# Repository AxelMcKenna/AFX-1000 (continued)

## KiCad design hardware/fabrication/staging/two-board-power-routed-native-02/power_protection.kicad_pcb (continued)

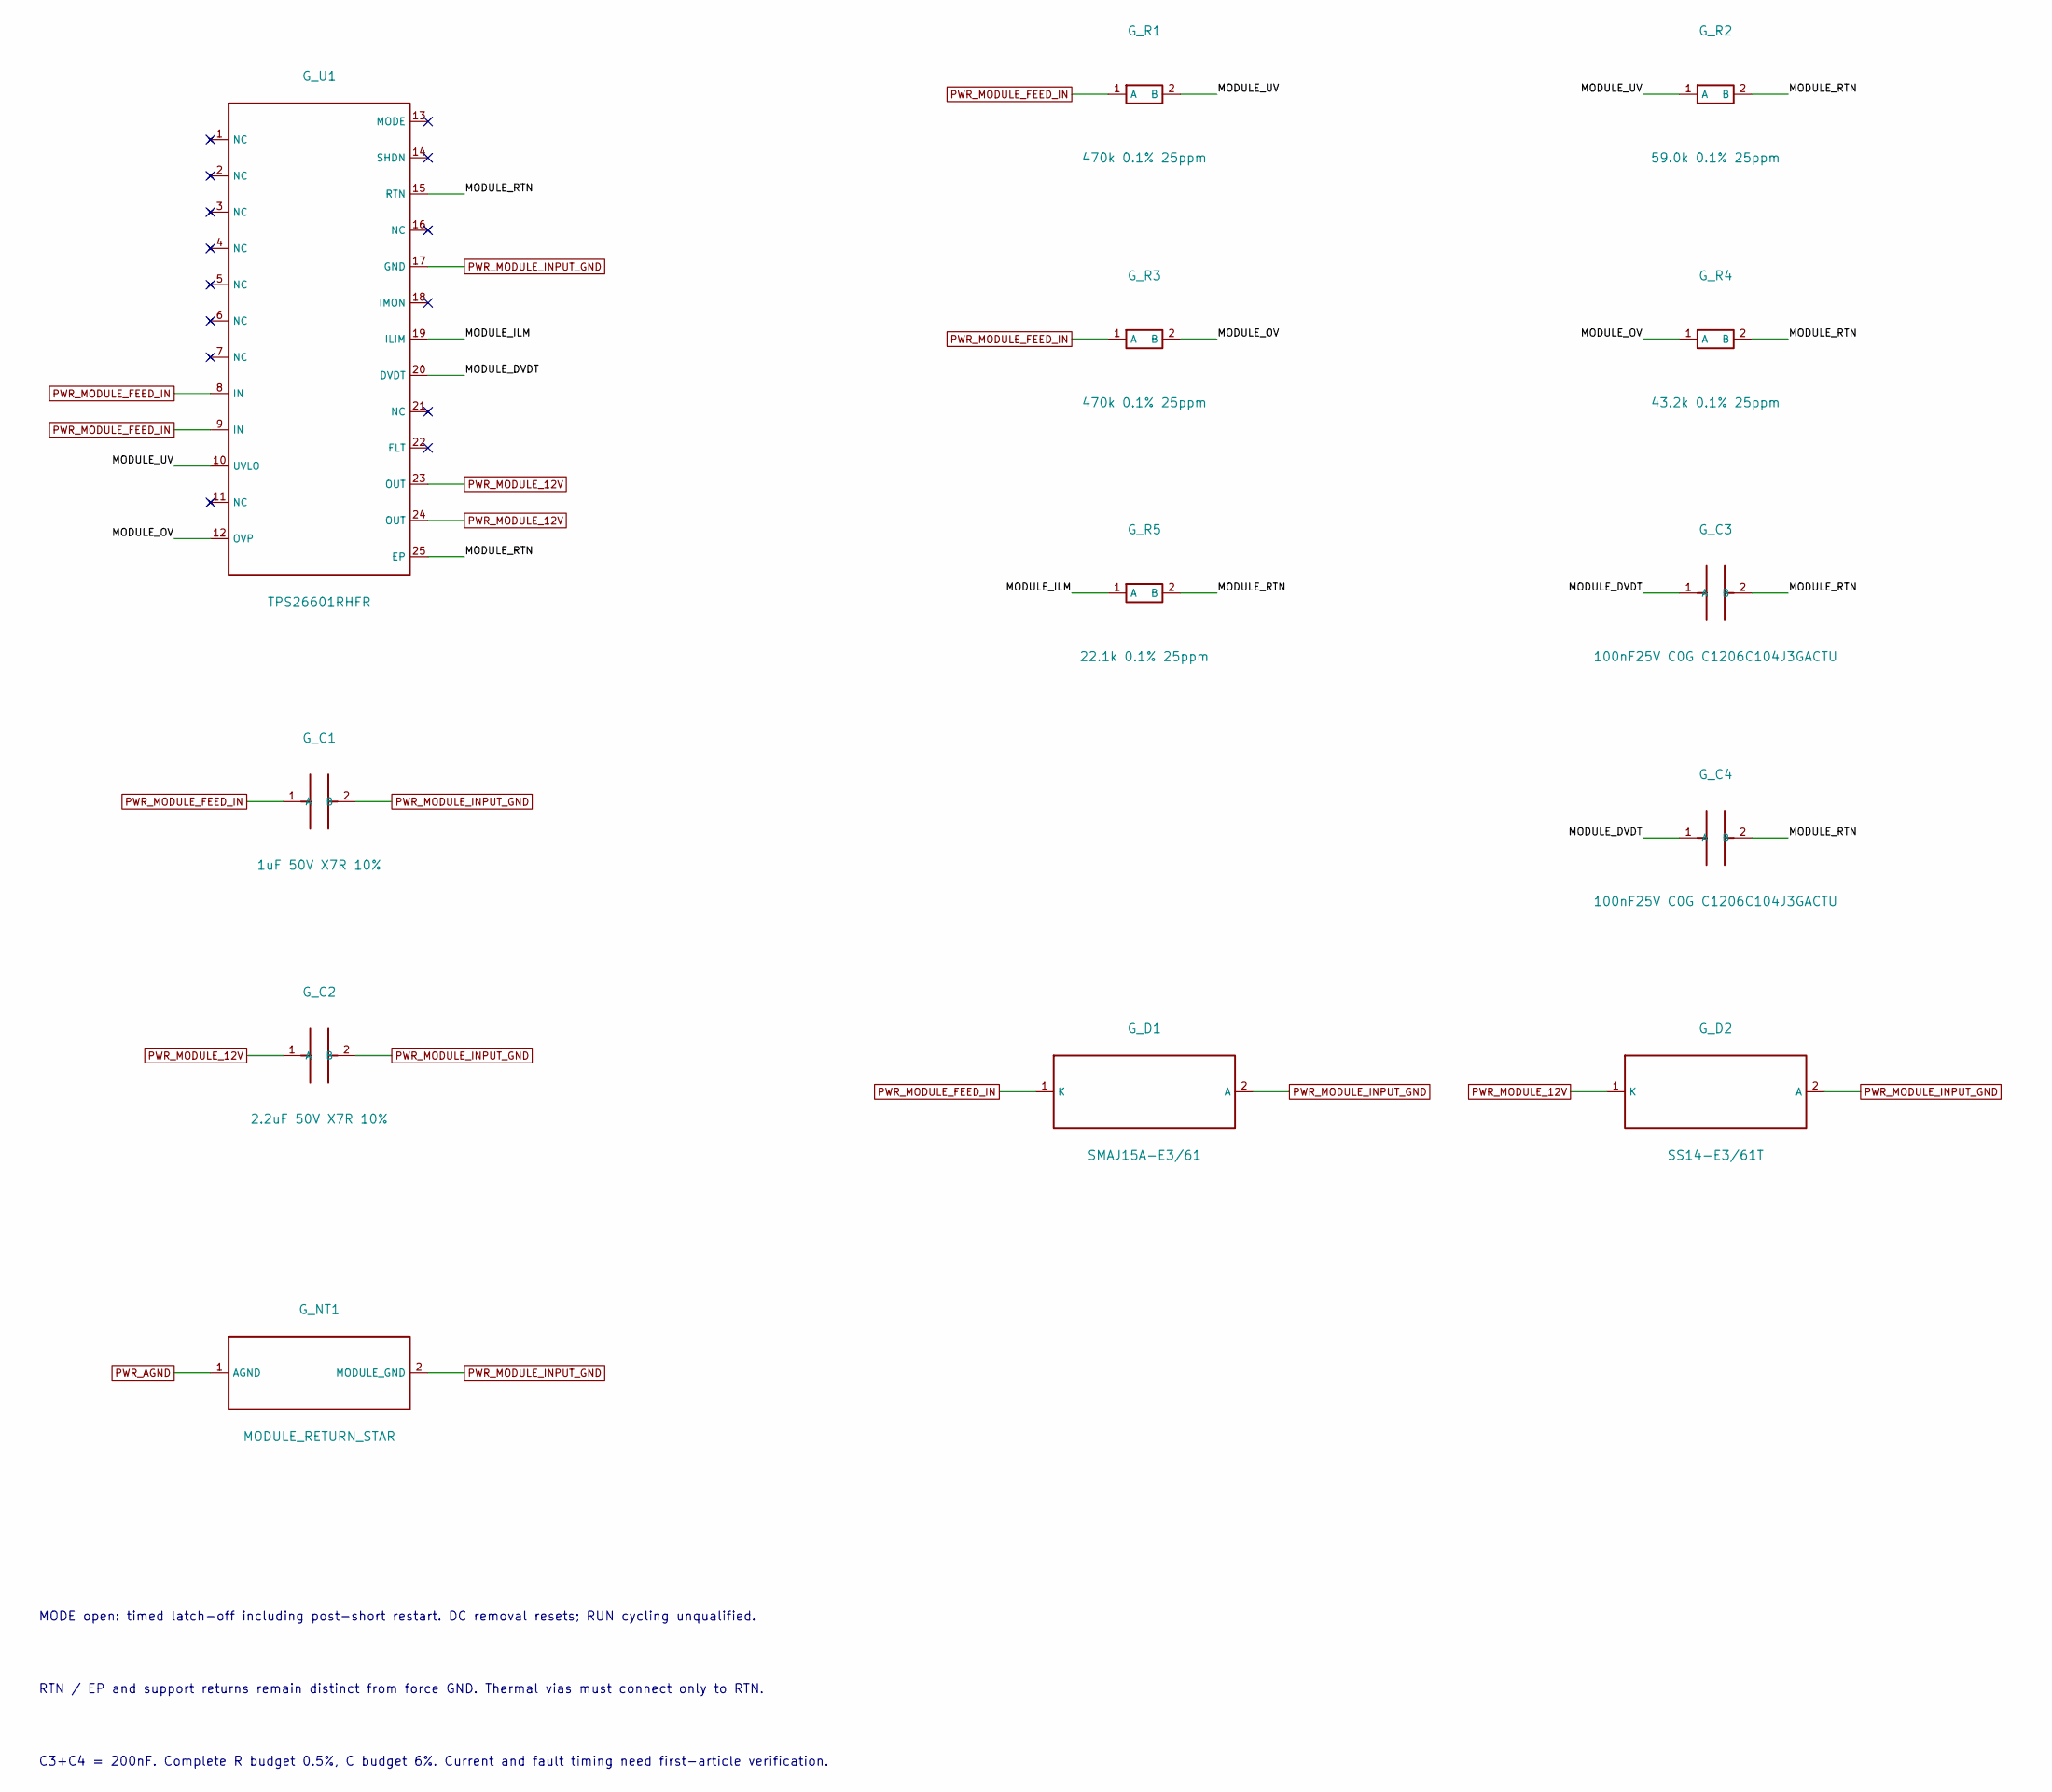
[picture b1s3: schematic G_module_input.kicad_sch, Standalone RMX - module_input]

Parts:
G_C1: 1uF 50V X7R 10%; C_0805_2012Metric
G_C2: 2.2uF 50V X7R 10%; C_1206_3216Metric
G_C3, G_C4: 100nF25V C0G C1206C104J3GACTU; PROPOSED_KEMET1206_LevelB
G_D1: SMAJ15A-E3/61; D_SMA
G_D2: SS14-E3/61T; D_SMA
G_NT1: MODULE_RETURN_STAR; Return_Star
G_R1, G_R3: 470k 0.1% 25ppm; R_0603_1608Metric
G_R2: 59.0k 0.1% 25ppm; R_0603_1608Metric
G_R4: 43.2k 0.1% 25ppm; R_0603_1608Metric
G_R5: 22.1k 0.1% 25ppm; R_0603_1608Metric
G_U1: TPS26601RHFR; TI_RHF0024A

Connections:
/G_module_input/MODULE_DVDT: G_C3.1 (A), G_C4.1 (A), G_U1.20 (DVDT)
/G_module_input/MODULE_ILM: G_R5.1 (A), G_U1.19 (ILIM)
/G_module_input/MODULE_OV: G_R3.2 (B), G_R4.1 (A), G_U1.12 (OVP)
/G_module_input/MODULE_RTN: G_C3.2 (B), G_C4.2 (B), G_R2.2 (B), G_R4.2 (B), G_R5.2 (B), G_U1.15 (RTN), G_U1.25 (EP)
/G_module_input/MODULE_UV: G_R1.2 (B), G_R2.1 (A), G_U1.10 (UVLO)
PWR_AGND: G_NT1.1 (AGND); also elsewhere on the board
PWR_MODULE_12V: G_C2.1 (A), G_D2.1 (K), G_U1.23 (OUT), G_U1.24 (OUT); also elsewhere on the board
PWR_MODULE_FEED_IN: G_C1.1 (A), G_D1.1 (K), G_R1.1 (A), G_R3.1 (A), G_U1.8 (IN), G_U1.9 (IN); also elsewhere on the board
PWR_MODULE_INPUT_GND: G_C1.2 (B), G_C2.2 (B), G_D1.2 (A), G_D2.2 (A), G_NT1.2 (MODULE_GND), G_U1.17 (GND); also elsewhere on the board

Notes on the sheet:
MODE open: timed latch-off including post-short restart. DC removal resets; RUN cycling unqualified.
RTN / EP and support returns remain distinct from force GND. Thermal vias must connect only to RTN.
C3+C4 = 200nF. Complete R budget 0.5%, C budget 6%. Current and fault timing need first-article verification.

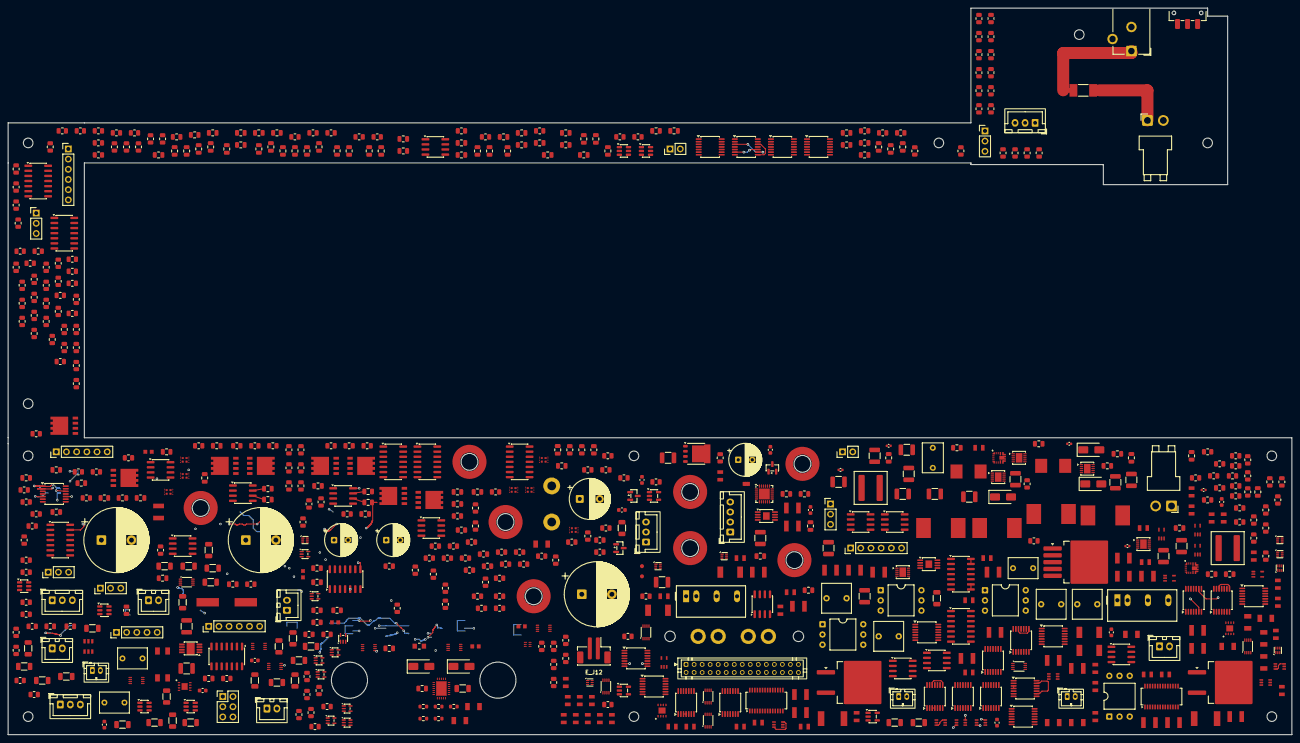
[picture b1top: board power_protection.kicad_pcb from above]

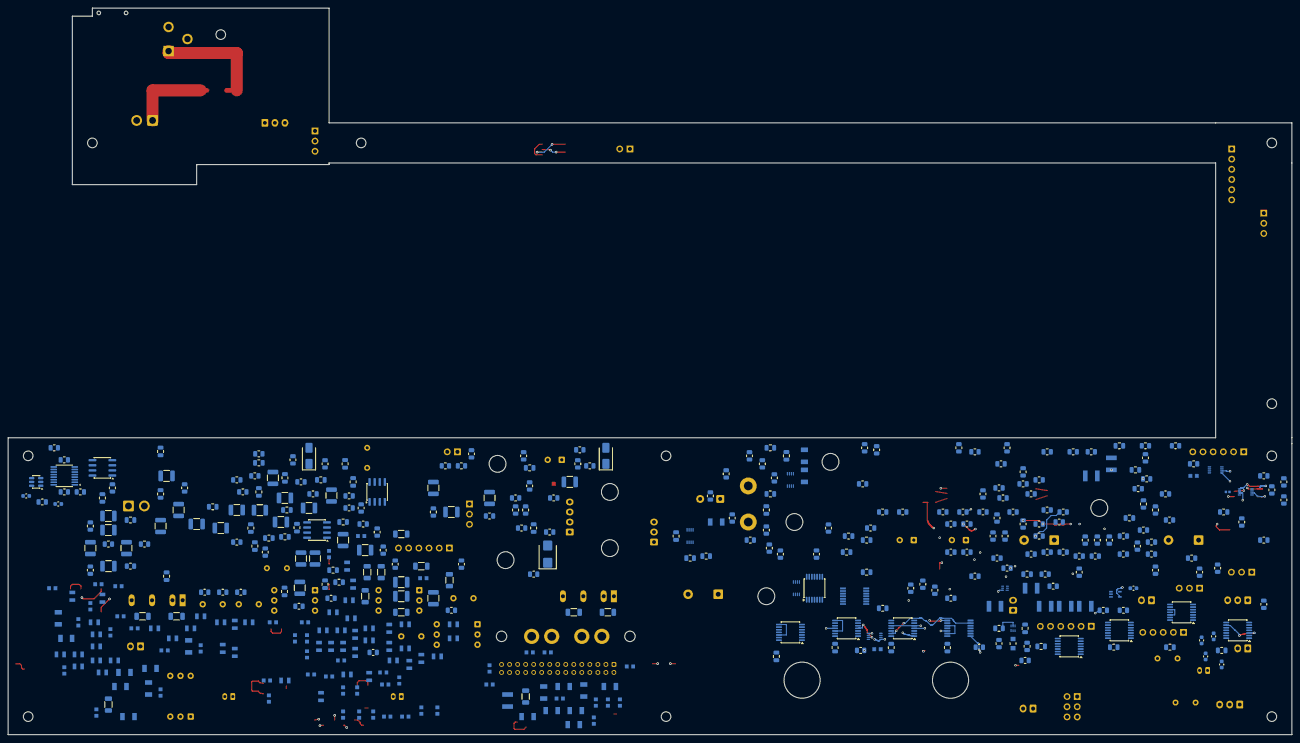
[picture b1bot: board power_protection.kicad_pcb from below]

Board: 8 copper layers, 320.0 x 181.1 mm, 1105 parts (410 on the bottom side), 635 nets.

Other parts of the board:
H_NEW1: PROPOSED_NPTH; H_NEW1
H_NEW2: PROPOSED_NPTH; H_NEW2
H_NEW3: PROPOSED_NPTH; H_NEW3
H_NEW4: PROPOSED_NPTH; H_NEW4
H_NEW5: PROPOSED_NPTH; H_NEW5
H_NEW6: PROPOSED_NPTH; H_NEW6
H_NEW7: PROPOSED_NPTH; H_NEW7
H_NEW8: PROPOSED_NPTH; H_NEW8
H_NEW9: PROPOSED_NPTH; H_NEW9
H_NEW10: PROPOSED_NPTH; H_NEW10
H_NEW11: PROPOSED_NPTH; H_NEW11
H_TOUCH1: PROPOSED_NPTH; H_TOUCH1
H_TOUCH2: PROPOSED_NPTH; H_TOUCH2
I_J2: B2PS-VH(LF)(SN); JST_VH_B2PS-VH_1x02_P3.96mm_Horizontal
N_H101, N_H102: STRAIN_POST_2p6_NPTH_RECEIVING
P_J101: JST B2PS-VH (VHR-2N/SVH-41T-P1.1 AWG16); JST_VH_B2PS-VH_1x02_P3.96mm_Horizontal

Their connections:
PWR_AGND: I_J2.2, P_J101.2; also elsewhere on the board
PWR_DC_IN: I_J2.1, P_J101.1; also elsewhere on the board
